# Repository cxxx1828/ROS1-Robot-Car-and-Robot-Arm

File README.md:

# ROS1 Mobile Manipulator Platform  
**Differential-Drive Robot with 5-DOF Robotic Arm – Full Stack from Hardware to Motion Planning**

A complete, production-grade robotics system integrating a mobile base and a 5-DOF manipulator, developed under **ROS Noetic** on Ubuntu 20.04.

This repository contains the entire development stack:
- Custom **hardware designs** (KiCad) for servo power distribution and current limiting
- **Low-level embedded drivers** in C++ (UART-based motor control, PWM generation, BLDC/servo feedback)
- **ROS hardware interface** with real-time joint state publishing and trajectory execution
- **MoveIt! motion planning** (OMPL, CHOMP, STOMP pipelines)
- Full **Gazebo simulation** and **RViz visualization**
- Comprehensive **teleoperation** (jogging, joypad, scripted routines)

---

### System Overview

| Component                  | Technology / Implementation                                      |
|----------------------------|------------------------------------------------------------------|
| Mobile Base                | Differential-drive / Ackermann steering, UART motor controllers  |
| Manipulator                | 5-DOF serial arm + parallel gripper                              |
| Motion Planning            | MoveIt! with multiple planners (RRTConnect, PRM, CHOMP, STOMP)   |
| Simulation                 | Gazebo 11 with physics, sensors, and plugin support              |
| Real-Time Control          | Custom C++ `robot_hw` interface (ROS Control compatible)         |
| Teleoperation              | Cartesian/space jogging, joypad mapping, scripted pick & place   |
| Power Electronics          | Custom KiCad shields: multi-channel servo current limiting       |
| Communication              | UART master-slave protocol with CRC8, real-time voltage logging  |

---

### Repository Structure
HW/                              → KiCad hardware designs
Servo_Motor_Shield_v1/       → Final servo power shield
Proto_Servo_Current_Limiter/ → Prototype current-limiting board
ROS/arm_and_chassis_ws/src/
s3a_main/                    → URDF, robot hardware interface, controllers
s3a_moveit_config/           → MoveIt! configuration and planning pipelines
arm_teleop/                  → Jogging and joypad teleoperation
common_teleop/               → Shared routines, pick-and-place sequences
wc_teleop/                   → Mobile base teleoperation
s3a_serial_main/             → UART motor controller master node
SW/Driver/motor_ctrl/            → Embedded C++ drivers (PWM, BLDC, servo)
SW/Test/                         → Unit and integration tests (waf build system)
text---

### Quick Start (Real Hardware & Simulation)

```bash
# Clone and build
mkdir -p ~/catkin_ws/src && cd ~/catkin_ws/src
git clone https://github.com/cxxx1828/ROS1-Robot-Car-and-Robot-Arm.git
cd ~/catkin_ws && catkin_make
source devel/setup.bash

# Real hardware launch
roslaunch s3a_main main.launch

# Simulation + MoveIt!
roslaunch s3a_moveit_config demo_gazebo.launch

# Teleoperation
roslaunch arm_teleop jog_teleop.launch          # Arm jogging
roslaunch wc_teleop manual_teleop.launch        # Drive base
roslaunch common_teleop routines_teleop.launch  # Pick & place demo

Key Demonstrations

Mobile manipulation with mounted arm
Precision pick-and-place (nail picking routine)
Real-time current/voltage monitoring via UART
Seamless switching between simulation and real hardware

Target Applications

Academic research in mobile manipulation
Industrial automation prototyping
Robotics education (ROS, MoveIt!, embedded systems)
Portfolio projects for robotics/software engineering roles

License
**
MIT License — free for academic, research, and commercial use.

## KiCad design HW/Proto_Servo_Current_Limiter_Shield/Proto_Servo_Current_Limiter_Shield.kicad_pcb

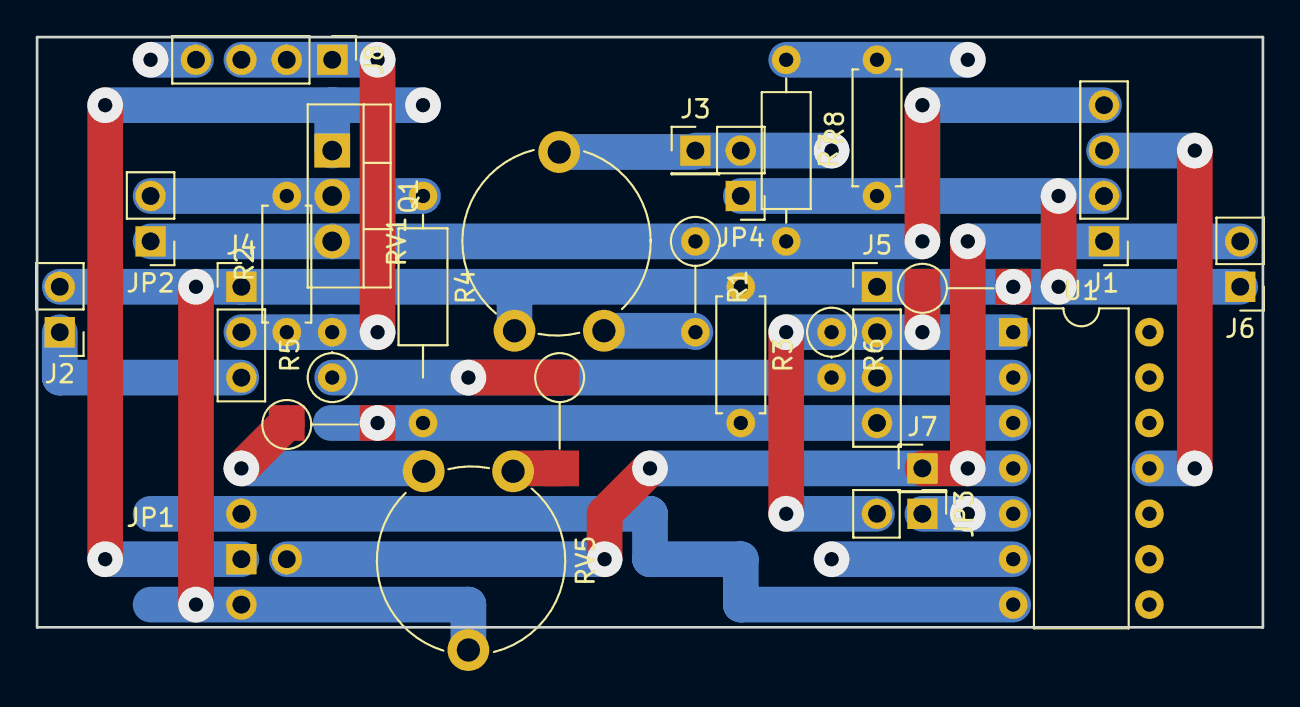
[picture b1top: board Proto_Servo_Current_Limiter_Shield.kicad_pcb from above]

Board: 2 copper layers, 68.6 x 33.0 mm, 27 parts (0 on the bottom side), 17 nets.

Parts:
J1, J5, J8: 1x4 2.54mm male; PinHeader_1x04_P2.54mm_Vertical
J2, J6: 1x2 2.54mm male; PinHeader_1x02_P2.54mm_Vertical
J3, J7: 1x1 2.54mm male; PinHeader_1x01_P2.54mm_Vertical
J4: 1x3 2.54mm male; PinHeader_1x03_P2.54mm_Vertical
JP1: Jumper_4_Bridged12; Jumper4_PinHeader_1x04_P2.54mm_Vertical
JP2, JP3, JP4: 1x2 2.54mm male; PinHeader_1x02_P2.54mm_Vertical
Q1: IRF4905; TO-220-3_Vertical
R1: 1k; R_Axial_DIN0207_L6.3mm_D2.5mm_P5.08mm_Vertical
R2: 0.1; R_Axial_DIN0207_L6.3mm_D2.5mm_P7.62mm_Horizontal
R3, R8: 100k; R_Axial_DIN0207_L6.3mm_D2.5mm_P7.62mm_Horizontal
R4: 10k; R_Axial_DIN0207_L6.3mm_D2.5mm_P12.70mm_Horizontal
R5: 10k; R_Axial_DIN0207_L6.3mm_D2.5mm_P2.54mm_Vertical
R6: 100k; R_Axial_DIN0207_L6.3mm_D2.5mm_P2.54mm_Vertical
R7: 10M; R_Axial_DIN0207_L6.3mm_D2.5mm_P10.16mm_Horizontal
R28, R29: 10k; R_Axial_DIN0207_L6.3mm_D2.5mm_Pinf_Vertical
R30: 1k; R_Axial_DIN0207_L6.3mm_D2.5mm_Pinf_Vertical
RV1, RV5: 1k; Potentiometer_Piher_PT-10-V10_Vertical
U1: LM324; DIP-14_W7.62mm

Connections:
+5V: J1.4, JP2.1 (A), Q1.3 (S), R1.1, R7.2
+12V: J1.1, J6.2, J7.1, JP1.3 (D), U1.4 (V+)
-12V: J1.3, U1.11 (V-)
/OUT0: J5.2, JP3.2 (B), R6.1, R30.1, U1.1
/PWM0: J2.1, J4.3
/ch0/COMP_OUT: JP1.2 (A), U1.7
/ch0/CTRL: JP1.1 (C), Q1.1 (G)
/ch0/N: J4.2, J8.1, J8.2, J8.3, R2.1, R5.2
/ch0/N_DISABLE: J3.1, JP4.2 (B), RV1.2, U1.6 (-)
/ch0/P: JP2.2 (B), Q1.2 (D), R2.2, R4.1
/ch0/sub/N: J5.3, R5.1, R6.2, R29.1, U1.2 (-)
/ch0/sub/P: J5.4, R3.2, R4.2, R28.2, U1.3 (+)
GND: J1.2, J2.2, J4.1, J5.1, J6.1, J8.4, JP1.4 (B), JP4.1 (A), R3.1, R8.1, R30.2, RV1.3, RV5.2
unnamed: JP3.1 (A), R7.1, R8.2, U1.5 (+)
unnamed: R1.2, RV1.1
unnamed: R28.1, RV5.1
unnamed: R29.2, RV5.3

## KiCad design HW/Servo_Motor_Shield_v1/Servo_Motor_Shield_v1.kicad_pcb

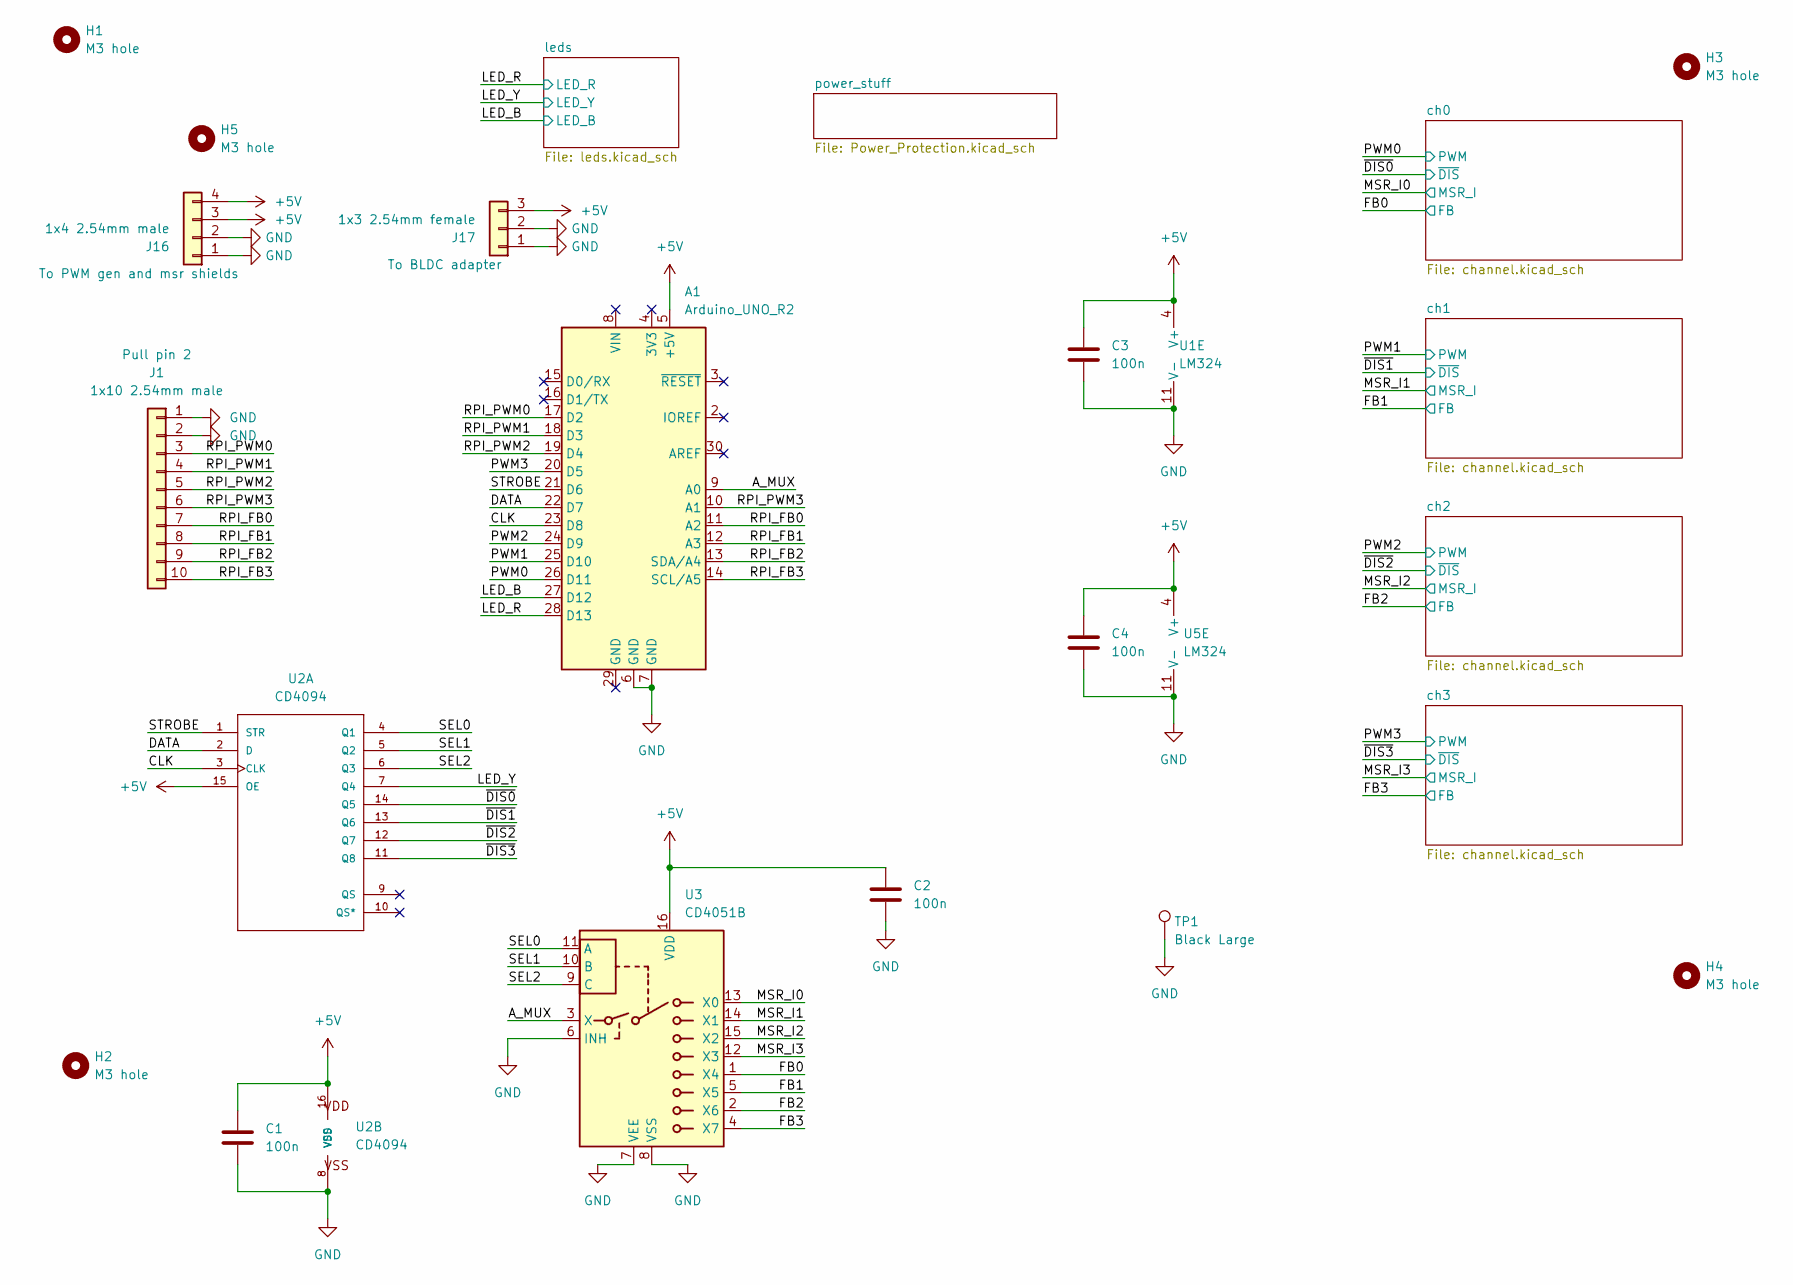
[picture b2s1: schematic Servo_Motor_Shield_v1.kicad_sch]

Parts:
A1: Arduino_UNO_R2; Arduino_UNO_R3_WithMountingHoles_Snapped_to_P2.54mm_Custom_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
C1, C2: 100n; C_Disc_D3.0mm_W1.6mm_P2.50mm
C3, C4: 100n; C_1206_3216Metric
H1, H2, H3, H4, H5: M3 hole; MountingHole_3.2mm_M3
J1: 1x10 2.54mm male; PinHeader_1x10_P2.54mm_Vertical
J16: 1x4 2.54mm male; PinHeader_1x04_P2.54mm_Vertical
J17: 1x3 2.54mm female; PinSocket_1x03_P2.54mm_Vertical
TP1: Black Large; TestPoint_THTPad_D2.0mm_Drill1.0mm
U1, U5: LM324; DIP-14_W7.62mm
U2: CD4094; DIP-16_W7.62mm
U3: CD4051B; DIP-16_W7.62mm

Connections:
+5V: A1.5 (+5V), C1.1, C2.1, C3.1, C4.1, J16.3, J16.4, J17.3, U1.4 (V+), U2.15 (OE), U2.16 (VDD), U3.16 (VDD), U5.4 (V+); also elsewhere on the board
/A_MUX: A1.9 (A0), U3.3 (X)
/CLK: A1.23 (D8), U2.3 (CLK)
/DATA: A1.22 (D7), U2.2 (D)
/FB0: U3.1 (X4); also elsewhere on the board
/FB1: U3.5 (X5); also elsewhere on the board
/FB2: U3.2 (X6); also elsewhere on the board
/FB3: U3.4 (X7); also elsewhere on the board
/LED_B: A1.27 (D12); also elsewhere on the board
/LED_R: A1.28 (D13); also elsewhere on the board
/LED_Y: U2.7 (Q4); also elsewhere on the board
/MSR_I0: U3.13 (X0); also elsewhere on the board
/MSR_I1: U1.8, U3.14 (X1); also elsewhere on the board
/MSR_I2: U3.15 (X2); also elsewhere on the board
/MSR_I3: U3.12 (X3), U5.8; also elsewhere on the board
/PWM0: A1.26 (D11); also elsewhere on the board
/PWM1: A1.25 (D10); also elsewhere on the board
/PWM2: A1.24 (D9); also elsewhere on the board
/PWM3: A1.20 (D5); also elsewhere on the board
/RPI_FB0: A1.11 (A2), J1.7
/RPI_FB1: A1.12 (A3), J1.8
/RPI_FB2: A1.13 (SDA/A4), J1.9
/RPI_FB3: A1.14 (SCL/A5), J1.10
/RPI_PWM0: A1.17 (D2), J1.3
/RPI_PWM1: A1.18 (D3), J1.4
/RPI_PWM2: A1.19 (D4), J1.5
/RPI_PWM3: A1.10 (A1), J1.6
/SEL0: U2.4 (Q1), U3.11 (A)
/SEL1: U2.5 (Q2), U3.10 (B)
/SEL2: U2.6 (Q3), U3.9 (C)
/STROBE: A1.21 (D6), U2.1 (STR)
/ch1/CTRL: U1.7; also elsewhere on the board
/ch1/sub/N_SUB: U1.9 (-); also elsewhere on the board
/ch1/sub/P_SUB: U1.10 (+); also elsewhere on the board
/ch3/CTRL: U5.7; also elsewhere on the board
/ch3/sub/N_SUB: U5.9 (-); also elsewhere on the board
/ch3/sub/P_SUB: U5.10 (+); also elsewhere on the board
/~DIS0: U2.14 (Q5); also elsewhere on the board
/~DIS1: U1.6 (-), U2.13 (Q6); also elsewhere on the board
/~DIS2: U2.12 (Q7); also elsewhere on the board
/~DIS3: U2.11 (Q8), U5.6 (-); also elsewhere on the board
GND: A1.6 (GND), A1.7 (GND), C1.2, C2.2, C3.2, C4.2, J1.1, J1.2, J16.1, J16.2, J17.1, J17.2, TP1.1, U1.11 (V-), U2.8 (VSS), U3.6 (INH), U3.7 (VEE), U3.8 (VSS), U5.11 (V-); also elsewhere on the board
unnamed 72: U1.5 (+); also elsewhere on the board
unnamed 74: U5.5 (+); also elsewhere on the board

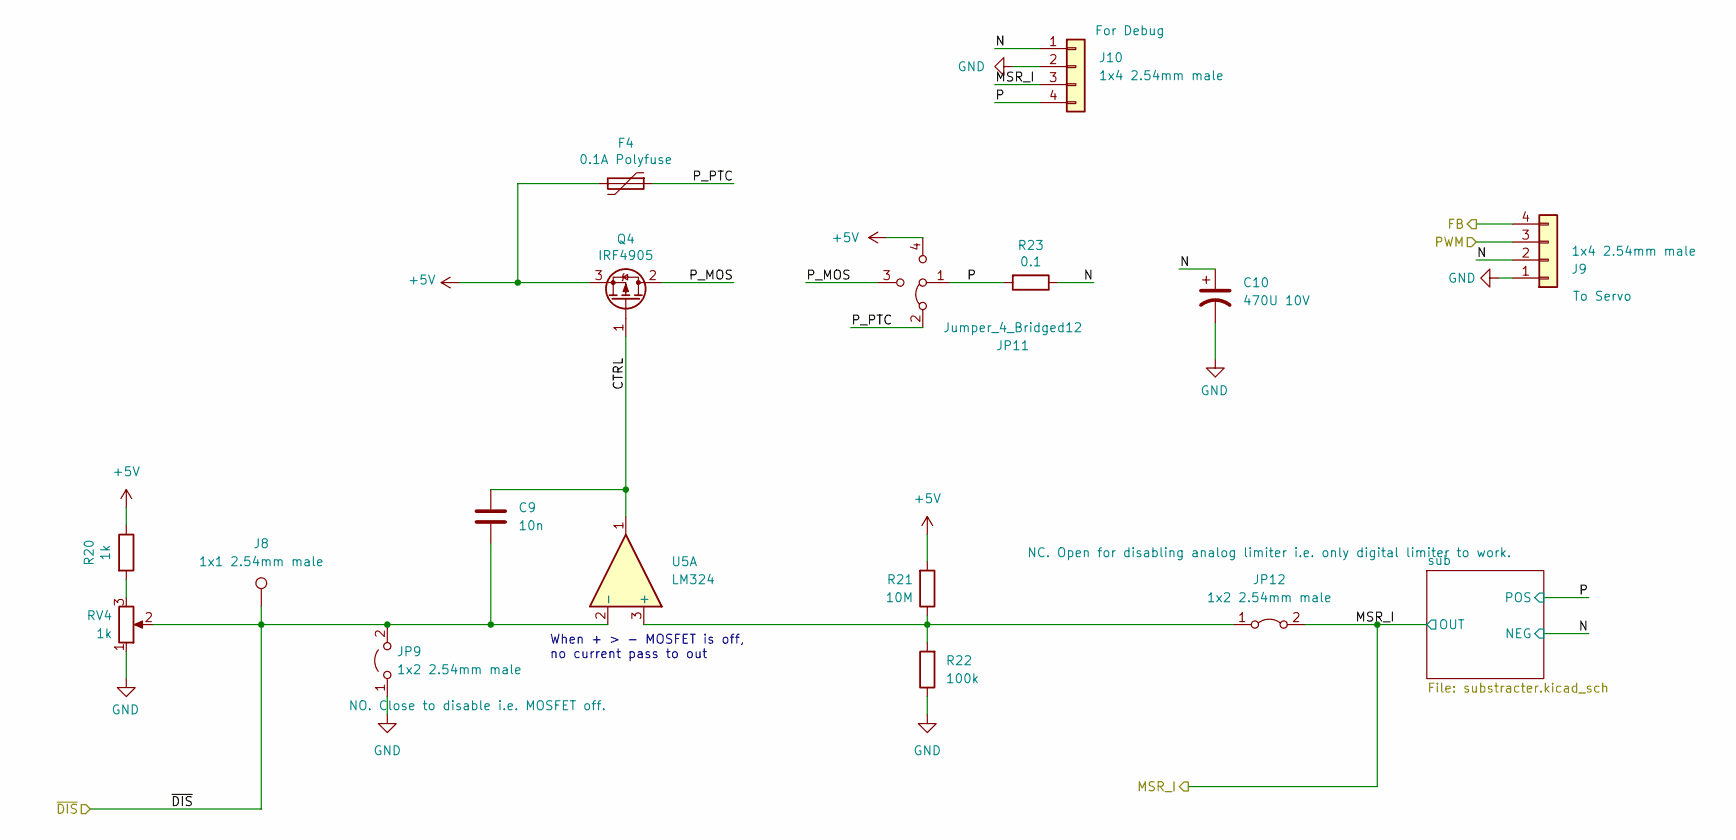
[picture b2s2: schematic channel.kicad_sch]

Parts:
C9: 10n; C_Disc_D3.0mm_W1.6mm_P2.50mm
C10: 470U 10V; CP_Radial_D10.0mm_P2.50mm
F4: 0.1A Polyfuse; C_Disc_D3.0mm_W1.6mm_P5.00mm
J8: 1x1 2.54mm male; PinHeader_1x01_P2.54mm_Vertical
J9, J10: 1x4 2.54mm male; PinHeader_1x04_P2.54mm_Vertical
JP9, JP12: 1x2 2.54mm male; PinHeader_1x02_P2.54mm_Vertical
JP11: Jumper_4_Bridged12; Jumper4_PinHeader_1x04_P2.54mm_Vertical
Q4: IRF4905; TO-220-3_Vertical
R20: 1k; R_Axial_DIN0207_L6.3mm_D2.5mm_P12.70mm_Horizontal
R21: 10M; R_Axial_DIN0207_L6.3mm_D2.5mm_P2.54mm_Vertical
R22: 100k; R_Axial_DIN0207_L6.3mm_D2.5mm_P7.62mm_Horizontal
R23: 0.1; R_Axial_DIN0207_L6.3mm_D2.5mm_P7.62mm_Horizontal
RV4: 1k; Potentiometer_Piher_PT-10-V10_Vertical
U5: LM324; DIP-14_W7.62mm

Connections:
+5V: F4.2, JP11.4 (B), Q4.3 (S), R20.1, R21.2; also elsewhere on the board
/FB2: J9.4; also elsewhere on the board
/MSR_I2: J10.3, JP12.2 (B); also elsewhere on the board
/MSR_I3: U5.8; also elsewhere on the board
/PWM2: J9.3; also elsewhere on the board
/ch2/CTRL: C9.1, Q4.1 (G), U5.1
/ch2/N: C10.1, J9.2, J10.1, R23.1; also elsewhere on the board
/ch2/P: J10.4, JP11.1 (C), R23.2; also elsewhere on the board
/ch2/P_MOS: JP11.3 (D), Q4.2 (D)
/ch2/P_PTC: F4.1, JP11.2 (A)
/ch3/CTRL: U5.7; also elsewhere on the board
/ch3/sub/N_SUB: U5.9 (-); also elsewhere on the board
/ch3/sub/P_SUB: U5.10 (+); also elsewhere on the board
/~DIS2: C9.2, J8.1, JP9.2 (B), RV4.2, U5.2 (-); also elsewhere on the board
/~DIS3: U5.6 (-); also elsewhere on the board
GND: C10.2, J9.1, J10.2, JP9.1 (A), R22.1, RV4.1; also elsewhere on the board
unnamed: JP12.1 (A), R21.1, R22.2, U5.3 (+)
unnamed 74: U5.5 (+); also elsewhere on the board
unnamed: R20.2, RV4.3

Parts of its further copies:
C5, C7, C11: 10n; C_Disc_D3.0mm_W1.6mm_P2.50mm
C6, C8, C12: 470U 10V; CP_Radial_D10.0mm_P2.50mm
F2, F3, F5: 0.1A Polyfuse; C_Disc_D3.0mm_W1.6mm_P5.00mm
J2, J3, J11: 1x1 2.54mm male; PinHeader_1x01_P2.54mm_Vertical
J4, J5, J6, J7, J12, J13: 1x4 2.54mm male; PinHeader_1x04_P2.54mm_Vertical
JP2, JP7, JP15: Jumper_4_Bridged12; Jumper4_PinHeader_1x04_P2.54mm_Vertical
JP3, JP4, JP5, JP8, JP13, JP16: 1x2 2.54mm male; PinHeader_1x02_P2.54mm_Vertical
Q1, Q2, Q5: IRF4905; TO-220-3_Vertical
R1, R9, R34: 1k; R_Axial_DIN0207_L6.3mm_D2.5mm_P12.70mm_Horizontal
R2, R12, R37: 0.1; R_Axial_DIN0207_L6.3mm_D2.5mm_P7.62mm_Horizontal
R7, R10, R35: 10M; R_Axial_DIN0207_L6.3mm_D2.5mm_P2.54mm_Vertical
R8, R11, R36: 100k; R_Axial_DIN0207_L6.3mm_D2.5mm_P7.62mm_Horizontal
RV1, RV2, RV7: 1k; Potentiometer_Piher_PT-10-V10_Vertical

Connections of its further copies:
+5V: F2.2, F3.2, F5.2, JP2.4 (B), JP7.4 (B), JP15.4 (B), Q1.3 (S), Q2.3 (S), Q5.3 (S), R1.1, R7.2, R9.1, R10.2, R34.1, R35.2; also elsewhere on the board
/FB0: J4.4; also elsewhere on the board
/FB1: J6.4; also elsewhere on the board
/FB3: J12.4; also elsewhere on the board
/MSR_I0: J5.3, JP3.2 (B); also elsewhere on the board
/MSR_I1: J7.3, JP8.2 (B); also elsewhere on the board
/MSR_I3: J13.3, JP16.2 (B); also elsewhere on the board
/PWM0: J4.3; also elsewhere on the board
/PWM1: J6.3; also elsewhere on the board
/PWM3: J12.3; also elsewhere on the board
/ch0/CTRL: C5.1, Q1.1 (G); also elsewhere on the board
/ch0/N: C6.1, J4.2, J5.1, R2.1; also elsewhere on the board
/ch0/P: J5.4, JP2.1 (C), R2.2; also elsewhere on the board
/ch0/P_MOS: JP2.3 (D), Q1.2 (D)
/ch0/P_PTC: F2.1, JP2.2 (A)
/ch1/CTRL: C7.1, Q2.1 (G); also elsewhere on the board
/ch1/N: C8.1, J6.2, J7.1, R12.1; also elsewhere on the board
/ch1/P: J7.4, JP7.1 (C), R12.2; also elsewhere on the board
/ch1/P_MOS: JP7.3 (D), Q2.2 (D)
/ch1/P_PTC: F3.1, JP7.2 (A)
/ch3/CTRL: C11.1, Q5.1 (G); also elsewhere on the board
/ch3/N: C12.1, J12.2, J13.1, R37.1; also elsewhere on the board
/ch3/P: J13.4, JP15.1 (C), R37.2; also elsewhere on the board
/ch3/P_MOS: JP15.3 (D), Q5.2 (D)
/ch3/P_PTC: F5.1, JP15.2 (A)
/~DIS0: C5.2, J3.1, JP4.2 (B), RV1.2; also elsewhere on the board
/~DIS1: C7.2, J2.1, JP5.2 (B), RV2.2; also elsewhere on the board
/~DIS3: C11.2, J11.1, JP13.2 (B), RV7.2; also elsewhere on the board
GND: C6.2, C8.2, C12.2, J4.1, J5.2, J6.1, J7.2, J12.1, J13.2, JP4.1 (A), JP5.1 (A), JP13.1 (A), R8.1, R11.1, R36.1, RV1.1, RV2.1, RV7.1; also elsewhere on the board
unnamed 71: JP3.1 (A), R7.1, R8.2; also elsewhere on the board
unnamed 72: JP8.1 (A), R10.1, R11.2; also elsewhere on the board
unnamed 74: JP16.1 (A), R35.1, R36.2; also elsewhere on the board
unnamed: R1.2, RV1.3
unnamed: R9.2, RV2.3
unnamed: R34.2, RV7.3

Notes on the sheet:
When + > - MOSFET is off, no current pass to out

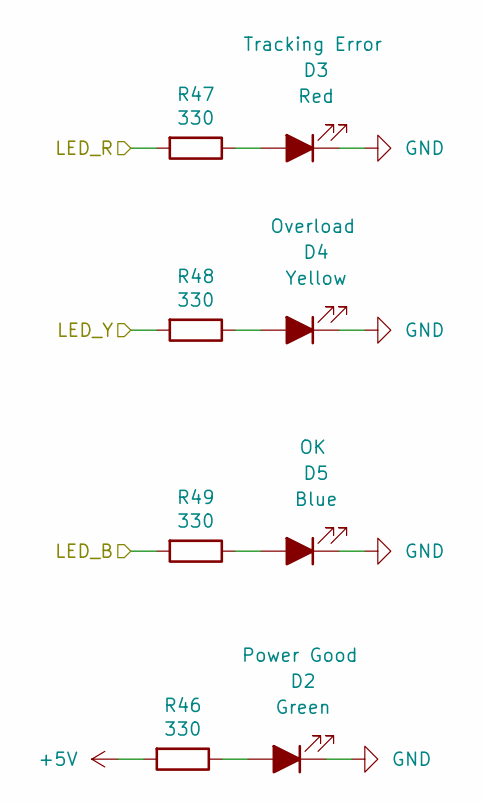
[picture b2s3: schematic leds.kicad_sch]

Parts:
D2: Green; LED_D3.0mm
D3: Red; LED_D3.0mm
D4: Yellow; LED_D3.0mm
D5: Blue; LED_D3.0mm
R46: 330; R_Axial_DIN0207_L6.3mm_D2.5mm_P2.54mm_Vertical
R47, R49: 330; R_Axial_DIN0207_L6.3mm_D2.5mm_P7.62mm_Horizontal
R48: 330; R_Axial_DIN0207_L6.3mm_D2.5mm_P5.08mm_Vertical

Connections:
+5V: R46.2; also elsewhere on the board
/LED_B: R49.2; also elsewhere on the board
/LED_R: R47.2; also elsewhere on the board
/LED_Y: R48.2; also elsewhere on the board
GND: D2.1 (K), D3.1 (K), D4.1 (K), D5.1 (K); also elsewhere on the board
unnamed: D2.2 (A), R46.1
unnamed: D3.2 (A), R47.1
unnamed: D4.2 (A), R48.1
unnamed: D5.2 (A), R49.1

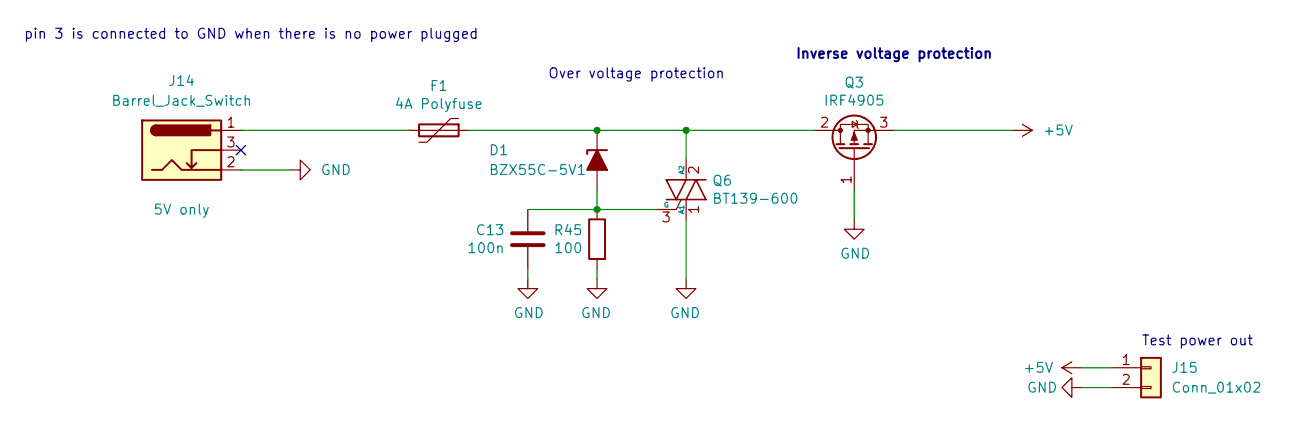
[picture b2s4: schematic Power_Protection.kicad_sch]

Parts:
C13: 100n; C_Disc_D3.0mm_W1.6mm_P5.00mm
D1: BZX55C-5V1; D_DO-35_SOD27_P2.54mm_Vertical_KathodeUp
F1: 4A Polyfuse; C_Disc_D3.0mm_W1.6mm_P5.00mm
J14: Barrel_Jack_Switch; BarrelJack_Horizontal
J15: Conn_01x02; PinHeader_1x02_P2.54mm_Vertical
Q3: IRF4905; TO-220-3_Vertical
Q6: BT139-600; TO-220-3_Vertical
R45: 100; R_Axial_DIN0207_L6.3mm_D2.5mm_P10.16mm_Horizontal

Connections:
+5V: J15.1, Q3.3 (S); also elsewhere on the board
GND: C13.1, J14.2, J15.2, Q3.1 (G), Q6.1 (A1), R45.2; also elsewhere on the board
unnamed: C13.2, D1.2 (A), Q6.3 (G), R45.1
unnamed: D1.1 (K), F1.1, Q3.2 (D), Q6.2 (A2)
unnamed: F1.2, J14.1

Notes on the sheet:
Inverse voltage protection
pin 3 is connected to GND when there is no power plugged
Test power out
Over voltage protection

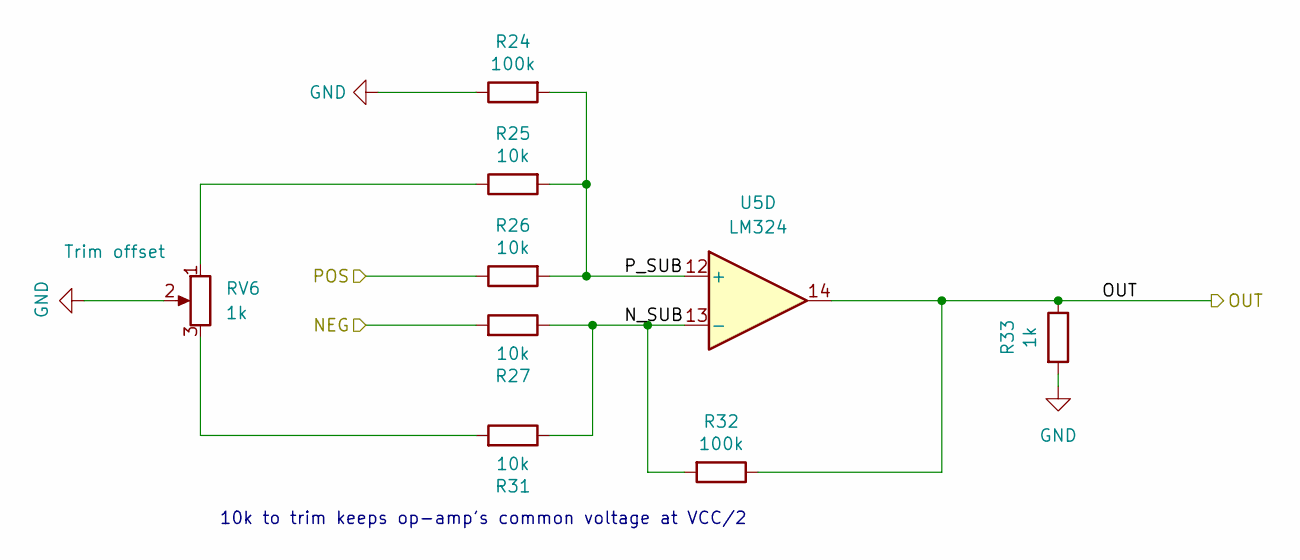
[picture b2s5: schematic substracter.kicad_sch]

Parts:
R24: 100k; R_Axial_DIN0207_L6.3mm_D2.5mm_P7.62mm_Horizontal
R25: 10k; R_Axial_DIN0207_L6.3mm_D2.5mm_P17.78mm_Horizontal
R26: 10k; R_Axial_DIN0207_L6.3mm_D2.5mm_P2.54mm_Vertical
R27: 10k; R_Axial_DIN0207_L6.3mm_D2.5mm_P7.62mm_Horizontal
R31: 10k; R_Axial_DIN0207_L6.3mm_D2.5mm_P15.24mm_Horizontal
R32: 100k; R_Axial_DIN0207_L6.3mm_D2.5mm_P2.54mm_Vertical
R33: 1k; R_Axial_DIN0207_L6.3mm_D2.5mm_P2.54mm_Vertical
RV6: 1k; Potentiometer_Piher_PT-10-V10_Vertical
U5: LM324; DIP-14_W7.62mm

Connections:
/MSR_I2: R32.1, R33.1, U5.14; also elsewhere on the board
/MSR_I3: U5.8; also elsewhere on the board
/ch2/N: R27.2; also elsewhere on the board
/ch2/P: R26.1; also elsewhere on the board
/ch2/sub/N_SUB: R27.1, R31.1, R32.2, U5.13 (-)
/ch2/sub/P_SUB: R24.2, R25.2, R26.2, U5.12 (+)
/ch3/CTRL: U5.7; also elsewhere on the board
/ch3/sub/N_SUB: U5.9 (-); also elsewhere on the board
/ch3/sub/P_SUB: U5.10 (+); also elsewhere on the board
/~DIS3: U5.6 (-); also elsewhere on the board
GND: R24.1, R33.2, RV6.2; also elsewhere on the board
unnamed 74: U5.5 (+); also elsewhere on the board
unnamed: R25.1, RV6.1
unnamed: R31.2, RV6.3

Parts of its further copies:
R3, R13, R38: 100k; R_Axial_DIN0207_L6.3mm_D2.5mm_P7.62mm_Horizontal
R4, R15, R40: 10k; R_Axial_DIN0207_L6.3mm_D2.5mm_P2.54mm_Vertical
R5, R16, R41: 10k; R_Axial_DIN0207_L6.3mm_D2.5mm_P7.62mm_Horizontal
R6, R18, R43: 100k; R_Axial_DIN0207_L6.3mm_D2.5mm_P2.54mm_Vertical
R14, R28, R39: 10k; R_Axial_DIN0207_L6.3mm_D2.5mm_P17.78mm_Horizontal
R17, R29, R42: 10k; R_Axial_DIN0207_L6.3mm_D2.5mm_P15.24mm_Horizontal
R19, R30, R44: 1k; R_Axial_DIN0207_L6.3mm_D2.5mm_P2.54mm_Vertical
RV3, RV5, RV8: 1k; Potentiometer_Piher_PT-10-V10_Vertical

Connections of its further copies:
/MSR_I0: R6.1, R30.1; also elsewhere on the board
/MSR_I1: R18.1, R19.1; also elsewhere on the board
/MSR_I3: R43.1, R44.1; also elsewhere on the board
/ch0/N: R5.2; also elsewhere on the board
/ch0/P: R4.1; also elsewhere on the board
/ch0/sub/N_SUB: R5.1, R6.2, R29.1; also elsewhere on the board
/ch0/sub/P_SUB: R3.2, R4.2, R28.2; also elsewhere on the board
/ch1/N: R16.2; also elsewhere on the board
/ch1/P: R15.1; also elsewhere on the board
/ch1/sub/N_SUB: R16.1, R17.1, R18.2; also elsewhere on the board
/ch1/sub/P_SUB: R13.2, R14.2, R15.2; also elsewhere on the board
/ch3/N: R41.2; also elsewhere on the board
/ch3/P: R40.1; also elsewhere on the board
/ch3/sub/N_SUB: R41.1, R42.1, R43.2; also elsewhere on the board
/ch3/sub/P_SUB: R38.2, R39.2, R40.2; also elsewhere on the board
GND: R3.1, R13.1, R19.2, R30.2, R38.1, R44.2, RV3.2, RV5.2, RV8.2; also elsewhere on the board
unnamed: R14.1, RV3.1
unnamed: R17.2, RV3.3
unnamed: R28.1, RV5.1
unnamed: R29.2, RV5.3
unnamed: R39.1, RV8.1
unnamed: R42.2, RV8.3

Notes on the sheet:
10k to trim keeps op-amp's common voltage at VCC/2

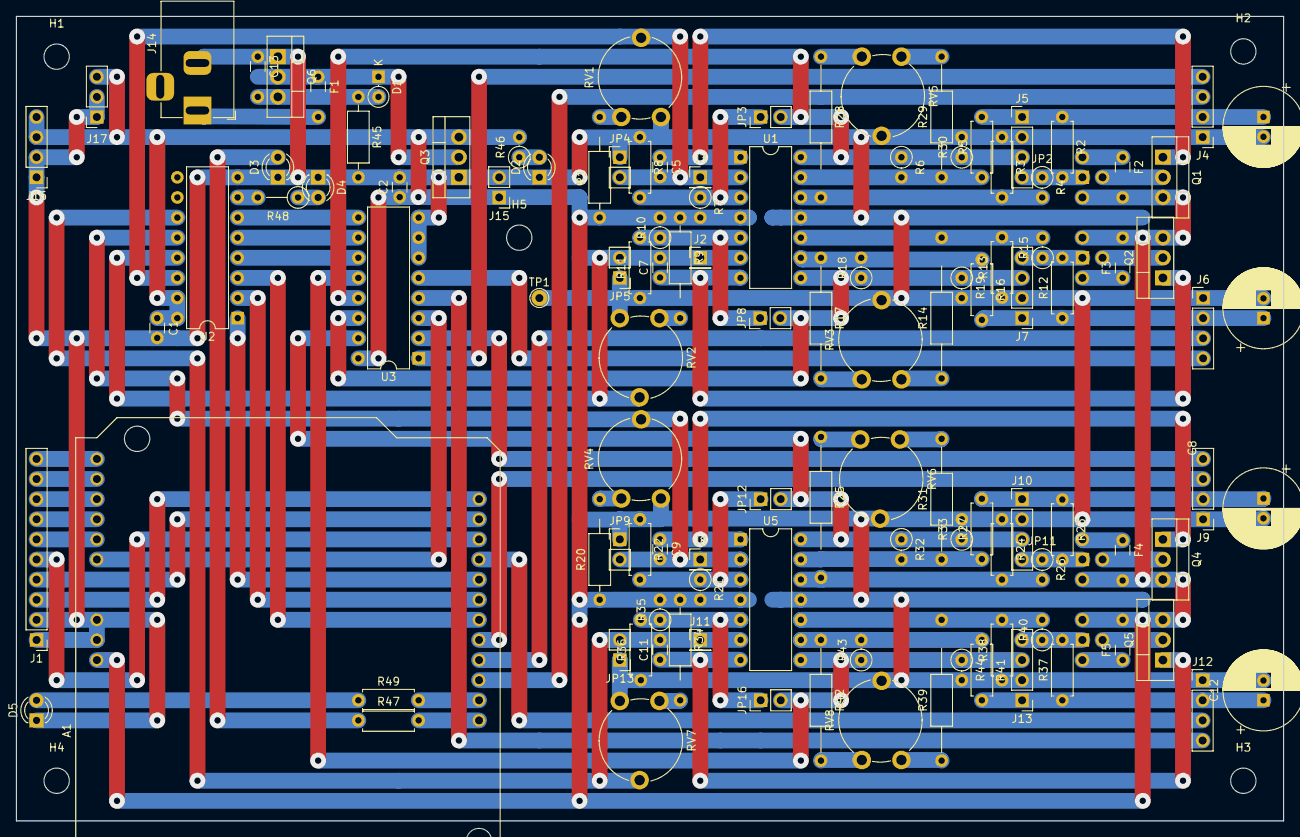
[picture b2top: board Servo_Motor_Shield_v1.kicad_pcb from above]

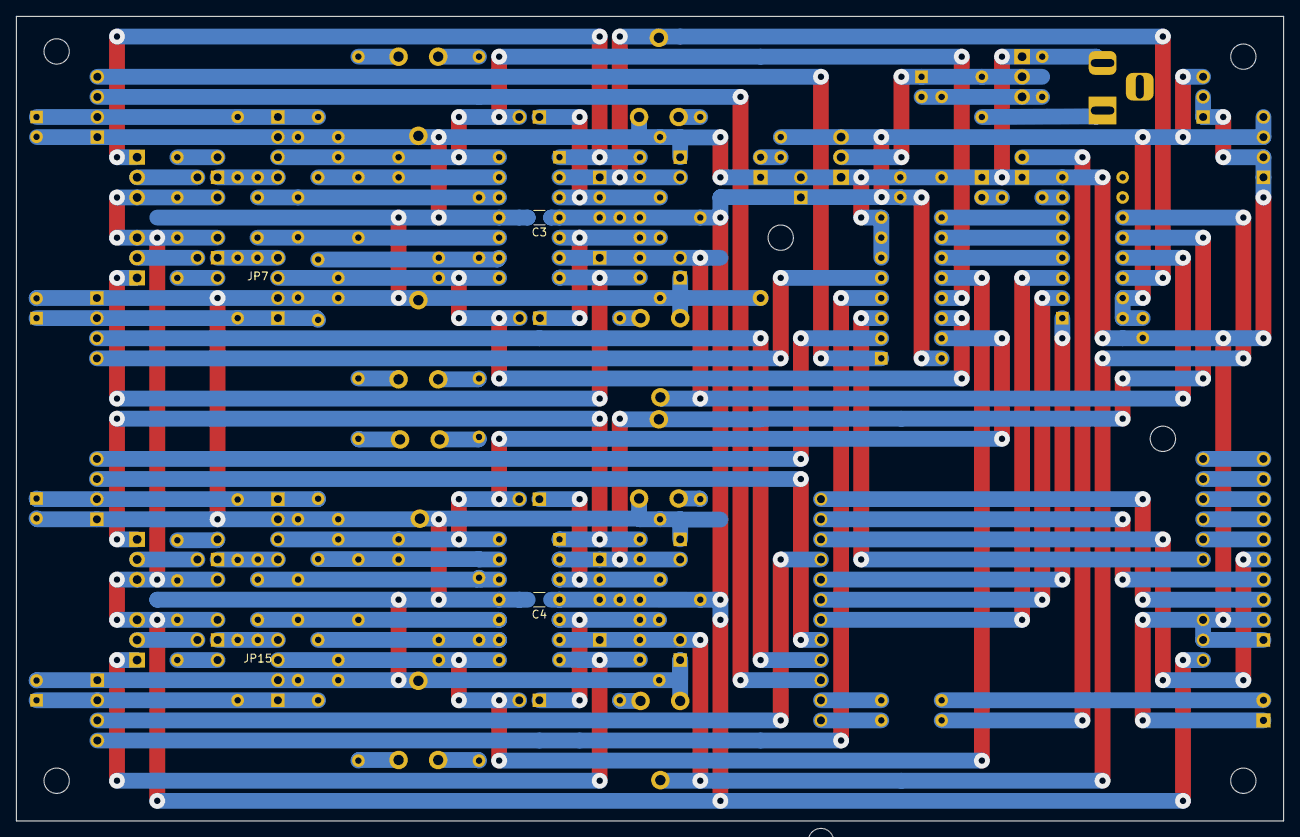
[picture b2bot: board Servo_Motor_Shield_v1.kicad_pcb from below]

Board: 2 copper layers, 160.0 x 101.6 mm, 126 parts (4 on the bottom side), 87 nets.

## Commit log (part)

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2025-11-28 feat: initial ROS1 robot car and arm workspace with Gazebo + MoveIt!
2025-11-28 Add README for ROS1 Mobile Manipulator Platform
    Added comprehensive documentation for the ROS1 Mobile Manipulator Platform, including system overview, repository structure, quick start instructions, key demonstrations, target applications, and lic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
